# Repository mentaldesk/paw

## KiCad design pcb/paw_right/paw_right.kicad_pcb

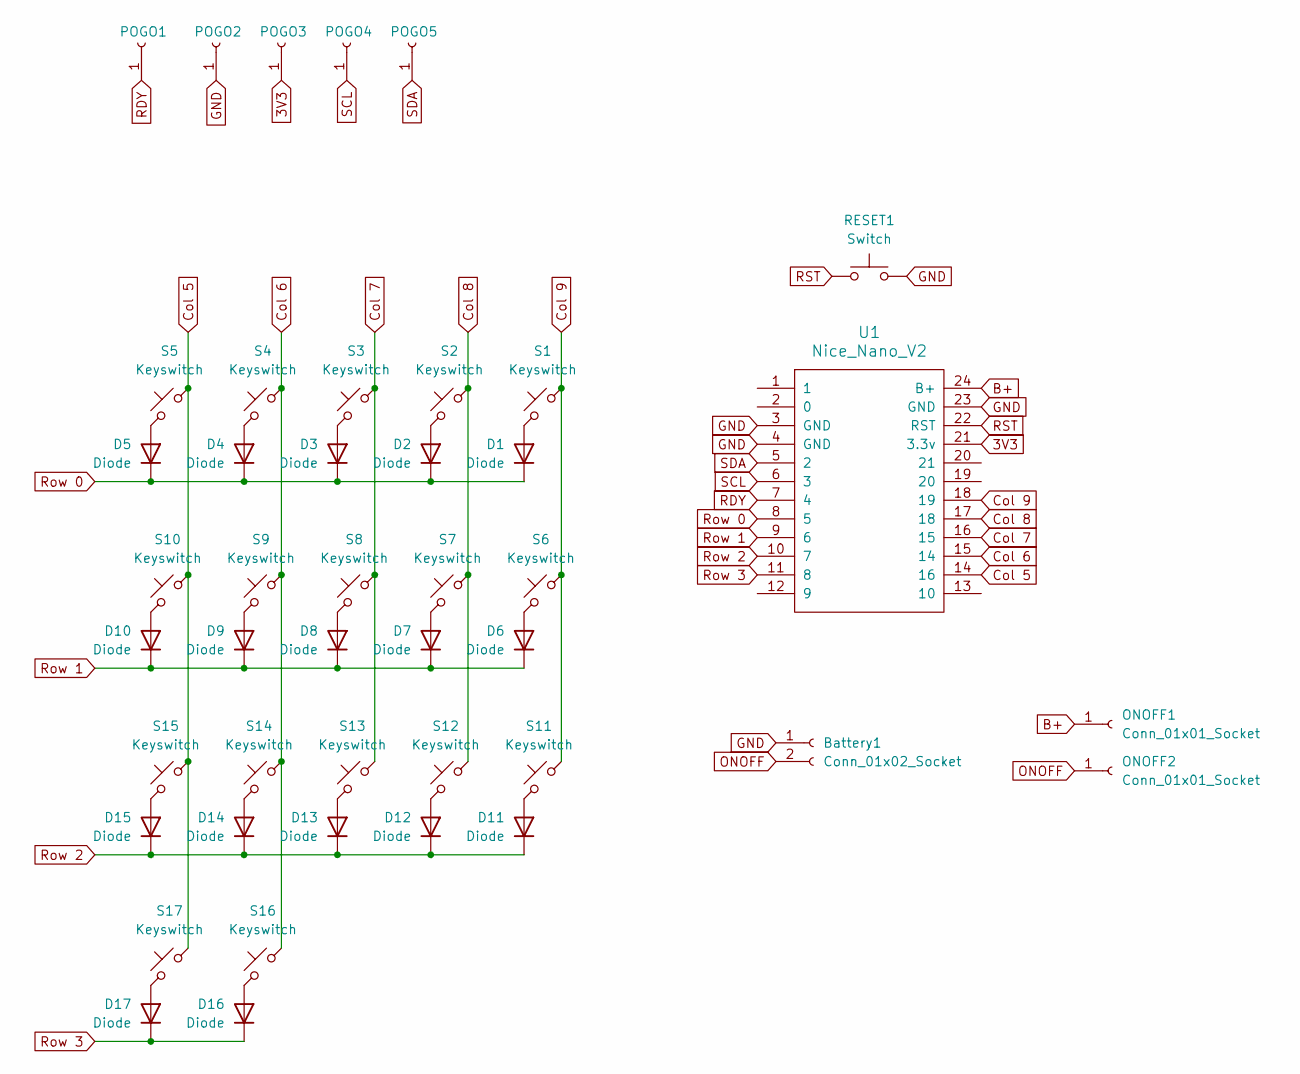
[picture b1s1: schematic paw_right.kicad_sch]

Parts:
Battery1: Conn_01x02_Socket; JST_PH_S2B-PH-K_1x02_P2.00mm_Horizontal
D1, D2, D3, D4, D5, D6, D7, D8, D9, D10, D11, D12, D13, D14, D15, D16, D17: Diode; Diode_DO-35
ONOFF1, ONOFF2: Conn_01x01_Socket; TestPoint_THTPad_1.5x1.5mm_Drill0.7mm
POGO1, POGO2, POGO3, POGO4, POGO5: Conn_01x01_Socket; TestPoint_THTPad_1.5x1.5mm_Drill0.7mm
RESET1: Switch; SW_TH_Tactile_Omron_B3F-100x
S1, S2, S3, S4, S5, S6, S7, S8, S9, S10, S11, S12, S13, S14, S15, S16, S17: Keyswitch; Hotswap_Choc_V1V2
U1: Nice_Nano_V2

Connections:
3V3: POGO3.1, U1.21 (3.3v)
B+: ONOFF1.1, U1.24 (B+)
Col 5: S5.1, S10.1, S15.1, S17.1, U1.14 (16)
Col 6: S4.1, S9.1, S14.1, S16.1, U1.15 (14)
Col 7: S3.1, S8.1, S13.1, U1.16 (15)
Col 8: S2.1, S7.1, S12.1, U1.17 (18)
Col 9: S1.1, S6.1, S11.1, U1.18 (19)
GND: Battery1.1, POGO2.1, RESET1.2, U1.3 (GND), U1.4 (GND), U1.23 (GND)
unnamed: D1.2 (A), S1.2
unnamed: D2.2 (A), S2.2
unnamed: D3.2 (A), S3.2
unnamed: D4.2 (A), S4.2
unnamed: D5.2 (A), S5.2
unnamed: D6.2 (A), S6.2
unnamed: D7.2 (A), S7.2
unnamed: D8.2 (A), S8.2
unnamed: D9.2 (A), S9.2
unnamed: D10.2 (A), S10.2
unnamed: D11.2 (A), S11.2
unnamed: D12.2 (A), S12.2
unnamed: D13.2 (A), S13.2
unnamed: D14.2 (A), S14.2
unnamed: D15.2 (A), S15.2
unnamed: D16.2 (A), S16.2
unnamed: D17.2 (A), S17.2
ONOFF: Battery1.2, ONOFF2.1
RDY: POGO1.1, U1.7 (4)
RST: RESET1.1, U1.22 (RST)
Row 0: D1.1 (K), D2.1 (K), D3.1 (K), D4.1 (K), D5.1 (K), U1.8 (5)
Row 1: D6.1 (K), D7.1 (K), D8.1 (K), D9.1 (K), D10.1 (K), U1.9 (6)
Row 2: D11.1 (K), D12.1 (K), D13.1 (K), D14.1 (K), D15.1 (K), U1.10 (7)
Row 3: D16.1 (K), D17.1 (K), U1.11 (8)
SCL: POGO4.1, U1.6 (3)
SDA: POGO5.1, U1.5 (2)

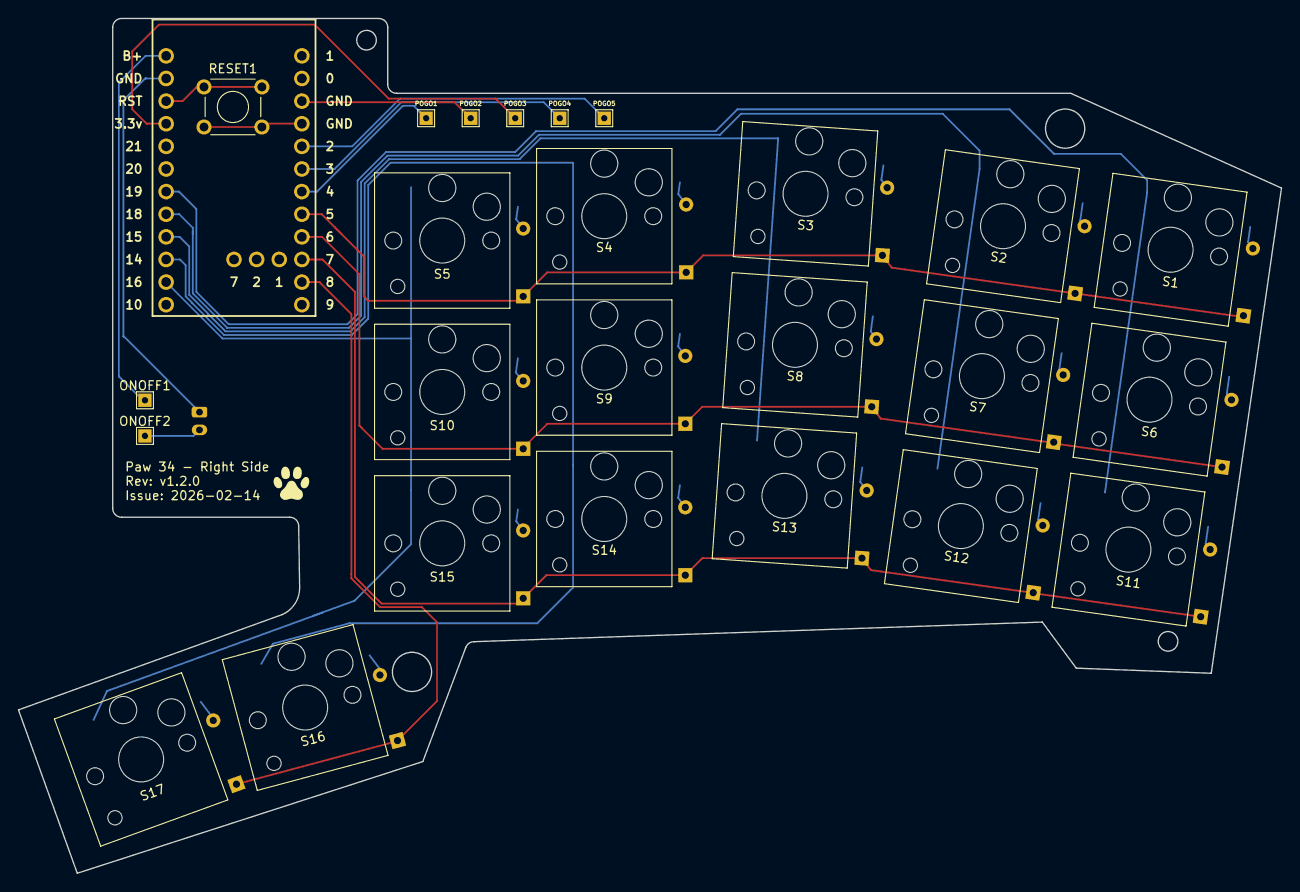
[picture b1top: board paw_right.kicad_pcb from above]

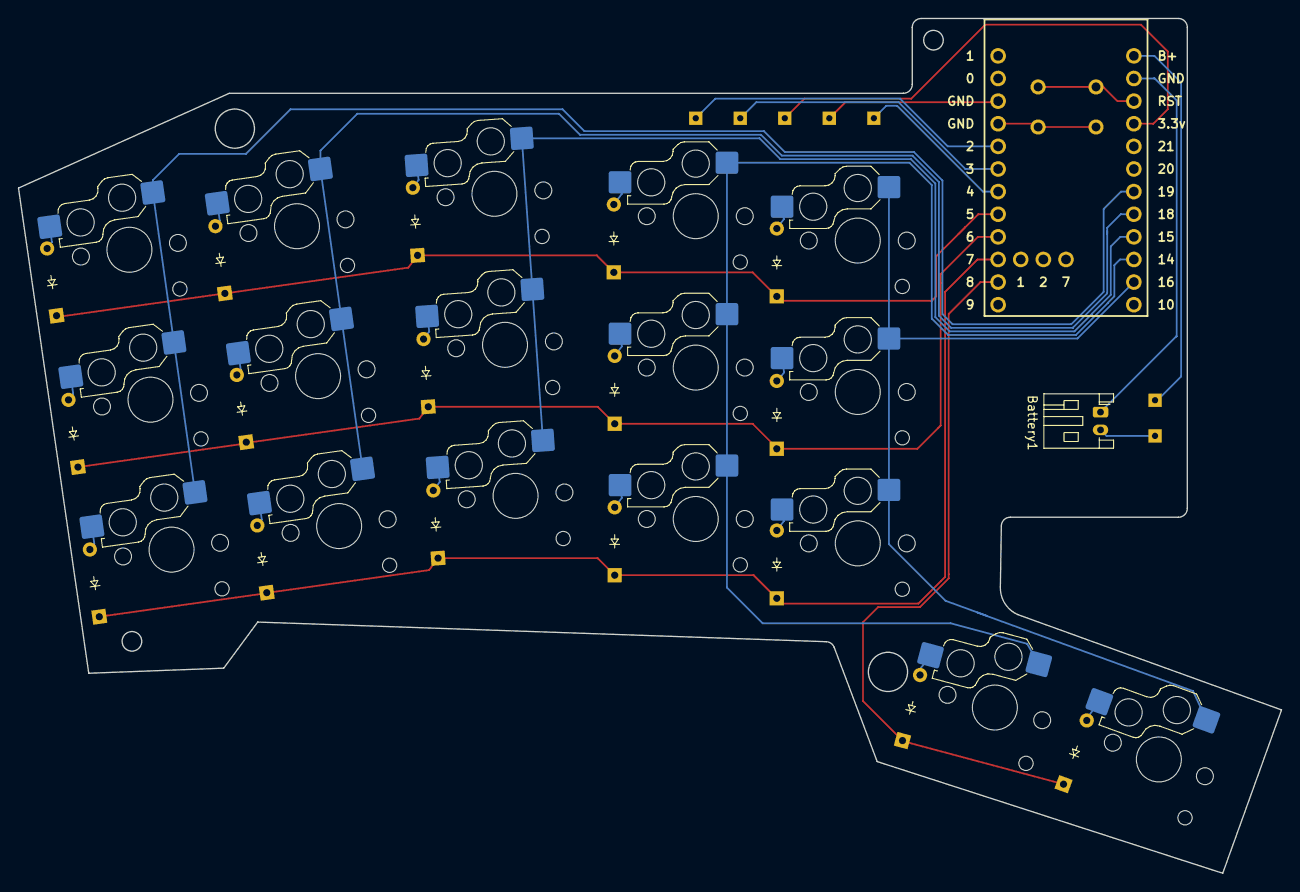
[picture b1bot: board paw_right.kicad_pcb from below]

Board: 2 copper layers, 141.8 x 96.0 mm, 44 parts (19 on the bottom side), 34 nets.

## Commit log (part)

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2025-11-22 Initial case design
2025-11-22 Trying a 5 column layout
2025-11-22 Second attempt at 5 col layout
2025-11-22 Add ZMK studio to build.yaml
2025-11-23 Updated case to avoid supports when printing
2025-11-23 Imported Oryx configuration
2025-11-23 Added missing momentary layer toggles
2025-11-23 Added additional support to the case bottom
2025-11-26 First working case
2025-11-26 Enable studio in shields
2025-12-04 Tweak keymap
2025-12-04 Update case
2025-12-04 Added meh keys
2025-12-05 Added a switch layer
2025-12-05 Added quick-release to sticky shift
2025-12-05 Increase timeout on OSMs
2025-12-06 Added a capslock combo
2025-12-07 Fixed hold-trigger-key-positions on thumb clusters
2025-12-07 Fixed col offset
2025-12-07 Fixed transform
2025-12-07 Added a keyboard layout for KLE
2025-12-07 Tweak tapping terms
2025-12-16 Trying vertical combos
2025-12-16 Try two finger home row combo for shift
2025-12-16 Move two finger combos off the home row
2025-12-16 Swapped OSM for shift and tab/backtick
2025-12-21 Added some combos to aleviate pinky pain
2025-12-21 fix duplicate node name
2025-12-25 Renamed to Paw
2026-01-23 Removed unecessary files
2026-01-23 Added a nice_nano_2 footprint to ergogen
2026-01-24 Added JST connector and power switch connectors to PCB
2026-01-24 Finished initial PCB design in Ergogen
2026-01-24 Added missing nets from thumb clusters
2026-01-24 Fix keymap
2026-01-25 Completed traces for lhs
2026-02-03 Reduce stagger on middle finger by 4mm
2026-02-12 Added pcb schema
2026-02-13 Added right hand PCB
2026-02-13 Added tracks
2026-02-28 Update GPIO pin mapping
2026-02-28 Fixed column mappings
2026-02-28 PCB rev 1.2.0
2026-02-28 Fix pin mapping for trackpad
2026-02-28 Added settings reset
2026-02-28 Updated to latest keymap
2026-03-02 Final case for the first build
2026-03-02 Default to macos on BLE1
2026-03-04 Moved OS selectors to top row to prevent accidental keypress
2026-03-04 Added reqire-idle-timeout to combos to prevent accidental triggering during rolls
2026-03-04 Move trackpad to RHS
2026-03-04 Add option to configure the trackpad on the left/central side
2026-03-04 Disable natural scroll by default
2026-03-06 Added OS agnosit windows management
2026-03-07 Refactored layers into separate files
2026-03-07 Tweaked window layer
2026-03-07 Tidied base layer
2026-03-07 Added command layer when holding f or u
2026-03-07 Tidy media layer
2026-03-08 Added an app switch layer
2026-03-08 Fixed media layer
2026-03-08 Remove redundant behaviour
2026-03-08 Added app search behaviours
2026-03-08 Added quit command
2026-03-08 Moved media and system layers around
2026-03-08 Use oskey/main instead of the branch
2026-03-08 Reduce tapping term for ok_app_search
2026-03-08 Added OS agnostic command layer (#6)
2026-03-08 Tweak tapping term for the app layer
2026-03-08 Emulate timeless HRM for the layer mod behaviour
2026-03-08 Increase tapping term for app layer mod behaviour
2026-03-08 Reduce tapping term
2026-03-08 Added a code command
2026-03-08 Revert to main branch for oskey
2026-03-09 Bump the tapping term for the app layer
2026-03-09 Added some commands for the IDEs
2026-03-09 Moved meh keys
2026-03-10 Add way to navigate to base layer to cmd and app layers
2026-03-10 Get stale keycode fix for oskey
2026-03-10 Go back to stable oskey release - fix merged
2026-03-11 Added link command
2026-03-11 Added a submit command
2026-03-11 Get latest fix for key sequence problem
2026-03-16 Removed shift combos
2026-03-16 Tweak tapping term for the app layer (#7)
2026-03-19 Remove require-prior-idle config on shift keys
2026-03-19 Try hold preferred on the left as well
2026-03-23 Add screenshot copy behavior to behaviors.dtsi
2026-03-23 Replace key binding with ok_scrn_cpy in media layer
2026-03-26 Add 4th bluetooth channel
2026-03-27 Tweak bottom row mods (#8)
    * Remove require-prior-idle config on shift keys
    * Try hold preferred on the left as well
    * Add 4th bluetooth channel
2026-03-27 Added Ubuntu shortcuts
2026-03-27 Added bluetooth switcher for Ubuntu
2026-03-30 Ubuntu (#9)
    * Remove require-prior-idle config on shift keys
    * Try hold preferred on the left as well
    * Add 4th bluetooth channel
    * Added Ubuntu shortcuts
    * Added bluetooth switcher for Ubuntu
    * .
2026-03-30 Change to QWERTY layout
2026-04-07 Chaged app search to Ubuntu default
